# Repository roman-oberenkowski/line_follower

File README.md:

# Line follower "Angler Fish"
Line following robot using image recognition (OpenCV)
# Documentation
[Documentation PDF (in Polish)](https://github.com/roman-oberenkowski/line_follower/blob/86b85e8dc0ec879baf128376f8ef6692d60e4e93/readme_resources/Dokumentacja.pdf)
# Demo
[Link to YouTube video](https://www.youtube.com/watch?v=mOt6cKBLhIQ)
# Rough schematic

# Real photo

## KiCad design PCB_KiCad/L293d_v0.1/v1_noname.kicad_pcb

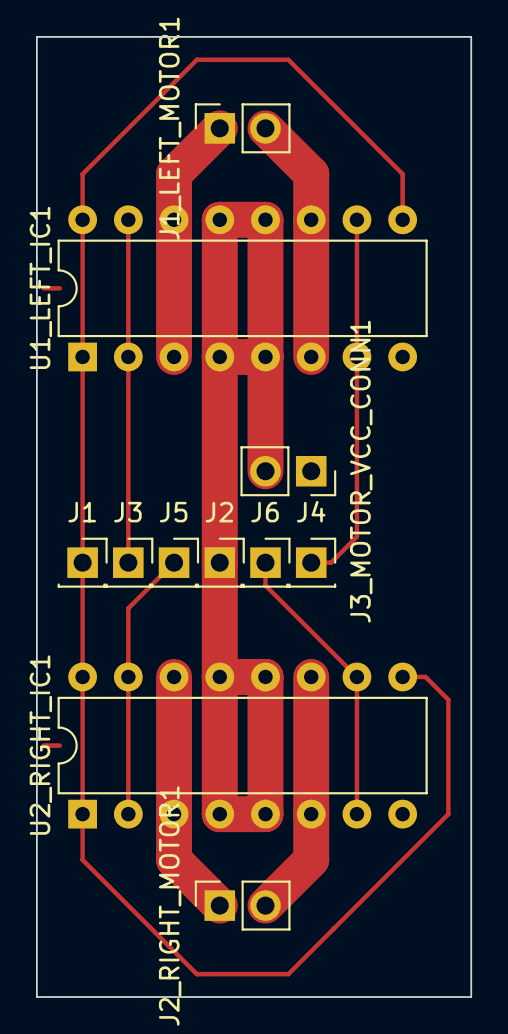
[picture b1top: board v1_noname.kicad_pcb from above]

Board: 2 copper layers, 24.1 x 53.3 mm, 11 parts (0 on the bottom side), 11 nets.

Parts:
J1, J2, J3, J4, J5, J6: Screw_Terminal_01x01; PinSocket_1x01_P2.54mm_Vertical
J1_LEFT_MOTOR1, J2_RIGHT_MOTOR1, J3_MOTOR_VCC_CONN1: Screw_Terminal_01x02; PinSocket_1x02_P2.54mm_Vertical
U1_LEFT_IC1, U2_RIGHT_IC1: L293D; DIP-16_W7.62mm

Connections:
unnamed: J1.1, U1_LEFT_IC1.1, U1_LEFT_IC1.9, U1_LEFT_IC1.16, U2_RIGHT_IC1.1, U2_RIGHT_IC1.9, U2_RIGHT_IC1.16
unnamed: J1_LEFT_MOTOR1.1, U1_LEFT_IC1.3, U1_LEFT_IC1.14
unnamed: J1_LEFT_MOTOR1.2, U1_LEFT_IC1.6, U1_LEFT_IC1.11
unnamed: J2.1, J3_MOTOR_VCC_CONN1.2, U1_LEFT_IC1.4, U1_LEFT_IC1.5, U1_LEFT_IC1.12, U1_LEFT_IC1.13, U2_RIGHT_IC1.4, U2_RIGHT_IC1.5, U2_RIGHT_IC1.12, U2_RIGHT_IC1.13
unnamed: J2_RIGHT_MOTOR1.1, U2_RIGHT_IC1.3, U2_RIGHT_IC1.14
unnamed: J2_RIGHT_MOTOR1.2, U2_RIGHT_IC1.6, U2_RIGHT_IC1.11
unnamed: J3.1, U1_LEFT_IC1.2, U1_LEFT_IC1.15
unnamed: J3_MOTOR_VCC_CONN1.1, U1_LEFT_IC1.8, U2_RIGHT_IC1.8
unnamed: J4.1, U1_LEFT_IC1.7, U1_LEFT_IC1.10
unnamed: J5.1, U2_RIGHT_IC1.2, U2_RIGHT_IC1.15
unnamed: J6.1, U2_RIGHT_IC1.7, U2_RIGHT_IC1.10

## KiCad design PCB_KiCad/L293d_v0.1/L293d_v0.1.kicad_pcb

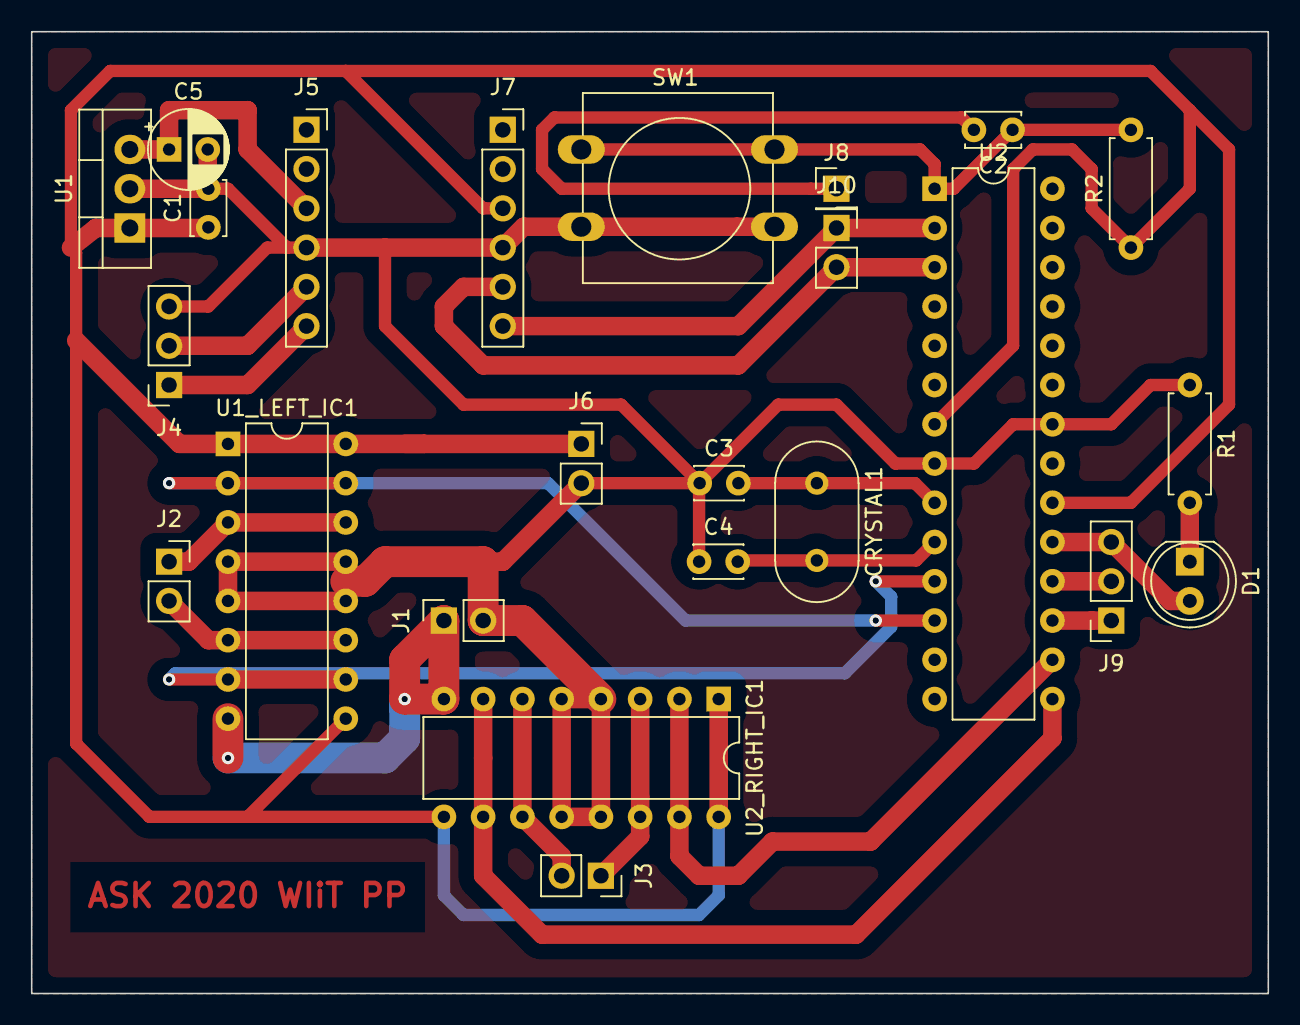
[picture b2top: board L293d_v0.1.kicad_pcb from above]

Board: 2 copper layers, 80.0 x 62.2 mm, 24 parts (0 on the bottom side), 24 nets.

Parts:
C1, C2: 100nF; C_Disc_D3.4mm_W2.1mm_P2.50mm
C3, C4: 22pF; C_Disc_D3.0mm_W2.0mm_P2.50mm
C5: 47uF; CP_Radial_D5.0mm_P2.50mm
CRYSTAL1: 16Mhz; Resonator-2Pin_W10.0mm_H5.0mm
D1: LED; LED_D5.0mm
J1: PIN_MOTOR_VCC_GND; PinSocket_1x02_P2.54mm_Vertical
J2: LEFT_MOTOR1; PinSocket_1x02_P2.54mm_Vertical
J3: RIGHT_MOTOR1; PinSocket_1x02_P2.54mm_Vertical
J4: PI_RX_TX_GND; PinSocket_1x03_P2.54mm_Vertical
J5: LV; PinSocket_1x06_P2.54mm_Vertical
J6: PIN_VCC_GND; PinSocket_1x02_P2.54mm_Vertical
J7: HV; PinSocket_1x06_P2.54mm_Vertical
J8: PIN_RESET; PinHeader_1x01_P2.54mm_Vertical
J9: GPIO; PinSocket_1x03_P2.54mm_Vertical
J10: PIN_RX_TX; PinSocket_1x02_P2.54mm_Vertical
R1: 330; R_Axial_DIN0207_L6.3mm_D2.5mm_P7.62mm_Horizontal
R2: 10K; R_Axial_DIN0207_L6.3mm_D2.5mm_P7.62mm_Horizontal
SW1: ResetButton; SW_PUSH-12mm
U1: LF33_TO220; TO-220-3_Vertical
U1_LEFT_IC1, U2_RIGHT_IC1: L293D; DIP-16_W7.62mm
U2: ATmega328-PU; DIP-28_W7.62mm

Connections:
+3V3: C5.1, J5.3, U1.3
+5V: C1.1, J6.1, J7.3, R2.1, U1.1, U1_LEFT_IC1.1, U1_LEFT_IC1.9, U1_LEFT_IC1.16, U2.7, U2.20, U2_RIGHT_IC1.1, U2_RIGHT_IC1.9, U2_RIGHT_IC1.16
Atmega_RX: J7.6, J10.1, U2.2
Atmega_TX: J7.5, J10.2, U2.3
GND: C1.2, C3.1, C4.1, C5.2, J1.2, J4.3, J5.4, J6.2, J7.4, R1.1, SW1.2, U1.2, U1_LEFT_IC1.4, U1_LEFT_IC1.5, U1_LEFT_IC1.12, U1_LEFT_IC1.13, U2.8, U2.22, U2_RIGHT_IC1.4, U2_RIGHT_IC1.5, U2_RIGHT_IC1.12, U2_RIGHT_IC1.13
Left_B: U1_LEFT_IC1.7, U1_LEFT_IC1.10, U2.11
Left_F: U1_LEFT_IC1.2, U1_LEFT_IC1.15, U2.12
unnamed: C2.1, R2.2, SW1.1, U2.1
unnamed: C2.2, J8.1
unnamed: C3.2, CRYSTAL1.1, U2.9
unnamed: C4.2, CRYSTAL1.2, U2.10
unnamed: D1.1, R1.2
unnamed: D1.2, J9.3, U2.19
unnamed: J1.1, U1_LEFT_IC1.8, U2_RIGHT_IC1.8
unnamed: J2.1, U1_LEFT_IC1.3, U1_LEFT_IC1.14
unnamed: J2.2, U1_LEFT_IC1.6, U1_LEFT_IC1.11
unnamed: J3.1, U2_RIGHT_IC1.3, U2_RIGHT_IC1.14
unnamed: J3.2, U2_RIGHT_IC1.6, U2_RIGHT_IC1.11
unnamed: J4.1, J5.6
unnamed: J4.2, J5.5
unnamed: J9.1, U2.17
unnamed: J9.2, U2.18
Right_B: U2.15, U2_RIGHT_IC1.7, U2_RIGHT_IC1.10
Right_F: U2.16, U2_RIGHT_IC1.2, U2_RIGHT_IC1.15

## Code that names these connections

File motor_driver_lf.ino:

#define RIGHT_B 9
#define RIGHT_F 10
#define LEFT_B 5
#define LEFT_F 6
#define LEFT 0
#define RIGHT 1
#define FORWARD 1
#define BACKWARD 0

int tab[2][2];

void set_motor_speed(int lr,int speed);

void setup() {
  pinMode(RIGHT_B,OUTPUT);
  pinMode(RIGHT_F,OUTPUT);
  pinMode(LEFT_B,OUTPUT);
  pinMode(LEFT_F,OUTPUT);
  pinMode(13,OUTPUT);
  tab[LEFT][FORWARD]=LEFT_F;
  tab[LEFT][BACKWARD]=LEFT_B;
  tab[RIGHT][BACKWARD]=RIGHT_B;
  tab[RIGHT][FORWARD]=RIGHT_F;
  Serial.begin(9600);
}


void loop() {
  while (Serial.available() > 0) {
    int left = Serial.parseInt();
    int right = Serial.parseInt();
    if (Serial.read() == '\n') {
      PORTB ^= (1<<PB5);
      int lspeed = scale(left);
      int rspeed = scale(right);
      set_motor_speed(LEFT,lspeed);
      set_motor_speed(RIGHT,rspeed);
      }
   }
   delay(100);
}


int scale(int value){ //-100,100 -> -255,-100 100,255
  if(value==0)return 0;
  value=constrain(value,-100,100);
  if(value<0)value=map(value,-100,0,-254,-100);
  else value=map(value,0,100,100,254);
  value=constrain(value,-255,255);
  Serial.println(value);
  return value;
}

void set_motor_speed(int lr,int speed){
  if(speed>0){
    digitalWrite(tab[lr][BACKWARD],LOW);
    analogWrite(tab[lr][FORWARD],speed);
  } 
  else if(speed<0){
    speed=-speed;
    digitalWrite(tab[lr][FORWARD],LOW);
    analogWrite(tab[lr][BACKWARD],speed);
  } 
  else{
    digitalWrite(tab[lr][FORWARD],LOW);
    digitalWrite(tab[lr][BACKWARD],LOW);
  }
}

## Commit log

2021-05-18 upload main code (raspberry pi)
2021-05-18 add motor driver (Arduino) code
2021-05-18 remove debug code
2021-05-18 photos
2021-05-18 add photos to readme
2021-05-19 datasheet and PCB proj
2022-04-12 add language note
